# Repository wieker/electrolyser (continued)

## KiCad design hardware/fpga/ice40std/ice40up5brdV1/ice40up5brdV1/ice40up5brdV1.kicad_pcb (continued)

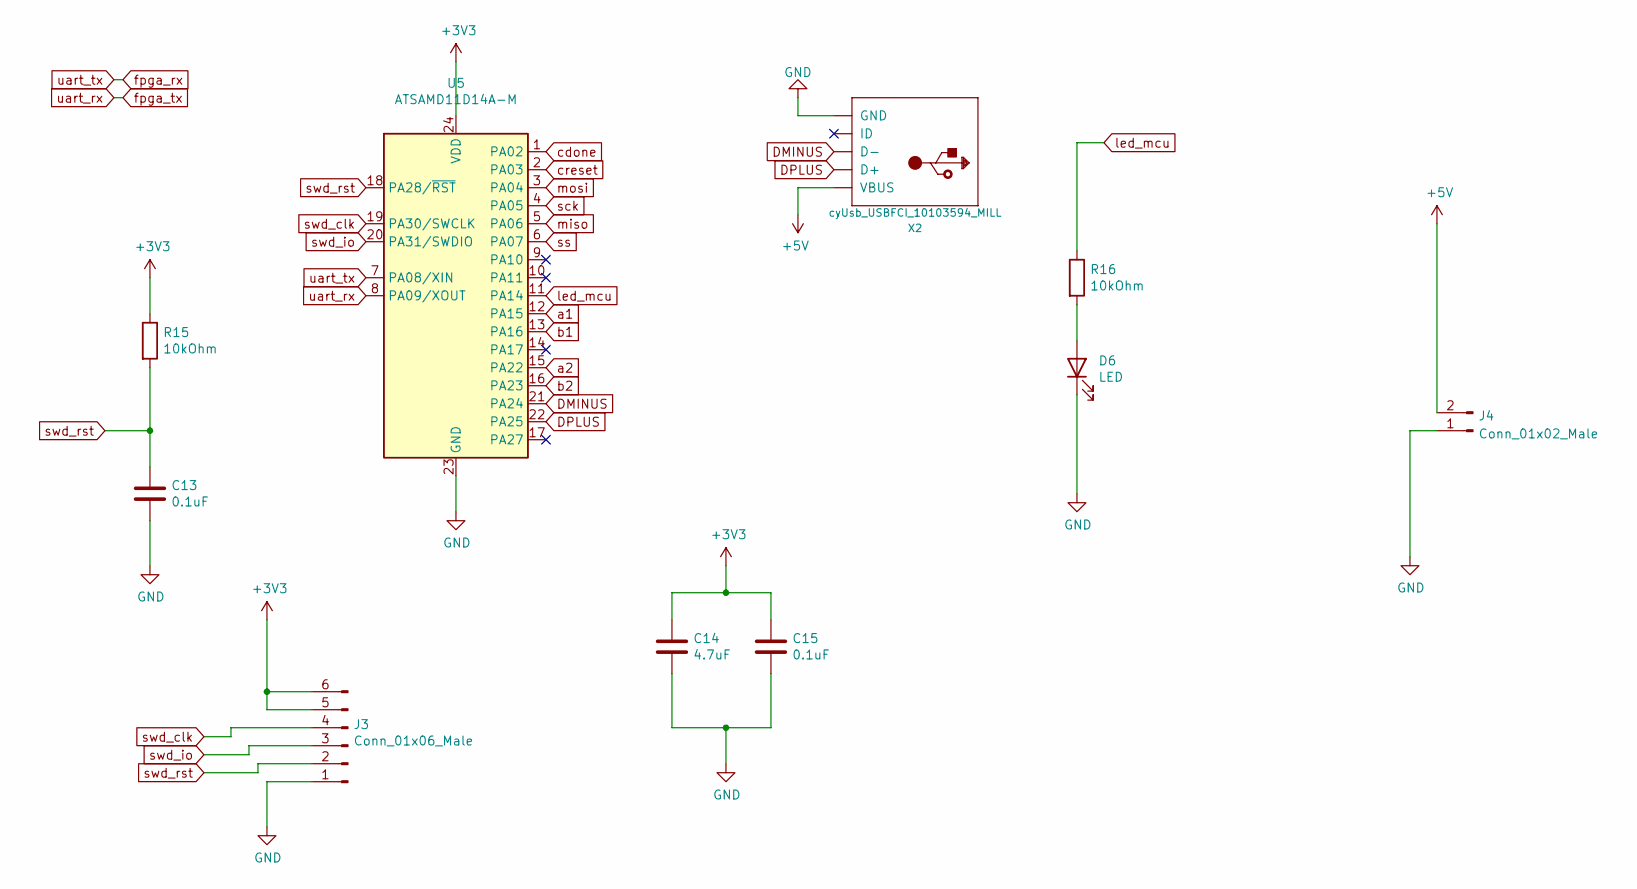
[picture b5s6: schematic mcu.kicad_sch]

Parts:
C13, C15: 0.1uF; C_0402_1005Metric
C14: 4.7uF; C_0402_1005Metric
D6: LED; LED_1206_3216Metric
J3: Conn_01x06_Male; PinHeader_1x06_P2.54mm_Vertical
J4: Conn_01x02_Male; PinHeader_1x02_P2.54mm_Horizontal
R15, R16: 10kOhm; R_0402_1005Metric
U5: ATSAMD11D14A-M; QFN-24-1EP_4x4mm_P0.5mm_EP2.6x2.6mm
X2: cyUsb_USBFCI_10103594_MILL; FCI_10103594_MILL

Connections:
+3V3: C14.1, C15.1, J3.5, J3.6, R15.1, U5.24 (VDD); also elsewhere on the board
+5V: J4.2, X2.VBUS; also elsewhere on the board
DMINUS: U5.21 (PA24), X2.D-
DPLUS: U5.22 (PA25), X2.D+
GND: C13.2, C14.2, C15.2, D6.1 (K), J3.1, J4.1, U5.23 (GND), X2.BASE@1 (GND), X2.BASE@2 (GND), X2.GND, X2.SPRT@1 (GND), X2.SPRT@2 (GND), X2.SPRT@3 (GND), X2.SPRT@4 (GND); also elsewhere on the board
unnamed: D6.2 (A), R16.2
a1: U5.12 (PA15); also elsewhere on the board
a2: U5.15 (PA22); also elsewhere on the board
b1: U5.13 (PA16); also elsewhere on the board
b2: U5.16 (PA23); also elsewhere on the board
cdone: U5.1 (PA02); also elsewhere on the board
creset: U5.2 (PA03); also elsewhere on the board
fpga_rx: U5.7 (PA08/XIN); also elsewhere on the board
fpga_tx: U5.8 (PA09/XOUT); also elsewhere on the board
led_mcu: R16.1, U5.11 (PA14)
miso: U5.5 (PA06); also elsewhere on the board
mosi: U5.3 (PA04); also elsewhere on the board
sck: U5.4 (PA05); also elsewhere on the board
ss: U5.6 (PA07); also elsewhere on the board
swd_clk: J3.4, U5.19 (PA30/SWCLK)
swd_io: J3.3, U5.20 (PA31/SWDIO)
swd_rst: C13.1, J3.2, R15.2, U5.18 (PA28/~RST)

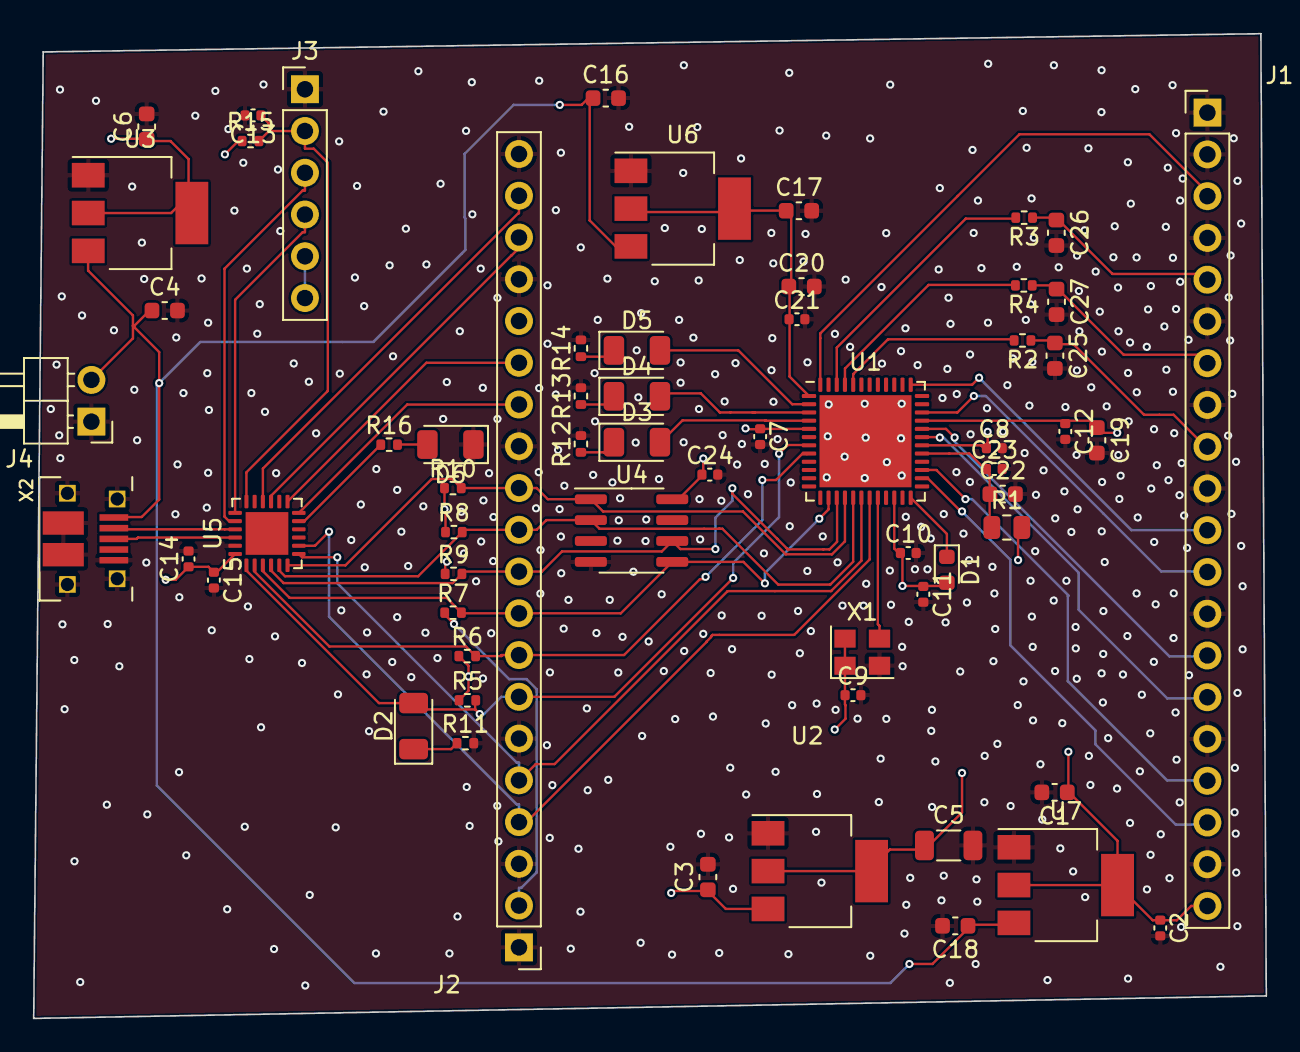
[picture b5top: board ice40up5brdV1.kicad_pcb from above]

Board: 4 copper layers, 75.0 x 59.9 mm, 62 parts (0 on the bottom side), 48 nets.

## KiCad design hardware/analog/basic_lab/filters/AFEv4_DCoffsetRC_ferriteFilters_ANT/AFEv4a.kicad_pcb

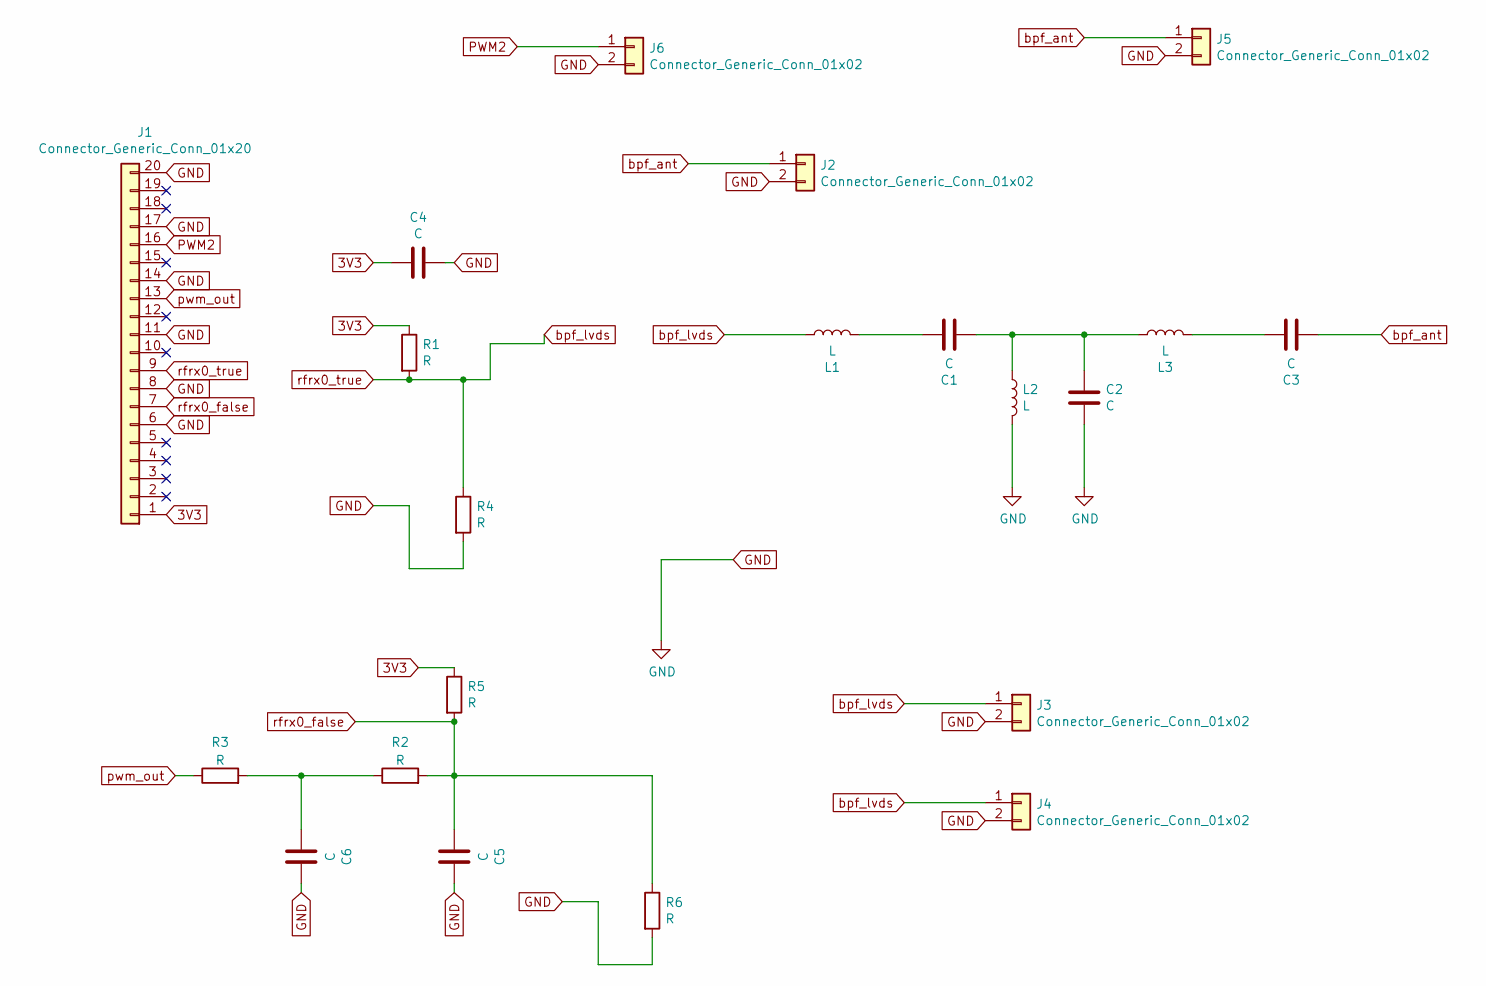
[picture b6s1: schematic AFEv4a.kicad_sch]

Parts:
C1, C2, C3, C4, C5, C6: C; C_Axial_L3.8mm_D2.6mm_P7.50mm_Horizontal
J1: Connector_Generic_Conn_01x20; PinHeader_1x20_P2.54mm_Vertical
J2, J3, J4, J5, J6: Connector_Generic_Conn_01x02; PinHeader_1x02_P2.54mm_Vertical
L1, L2, L3: L; L_Toroid_Horizontal_D12.7mm_P20.00mm_Diameter14-5mm_Amidon-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
R1, R2, R3, R4, R5, R6: R; R_Axial_DIN0207_L6.3mm_D2.5mm_P5.08mm_Vertical

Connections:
3V3: C4.2, J1.1, R1.1, R5.1
GND: C2.2, C4.1, C5.1, C6.1, J1.6, J1.8, J1.11, J1.14, J1.17, J1.20, J2.2, J3.2, J4.2, J5.2, J6.2, L2.2, R4.2, R6.2
unnamed: C1.1, L1.2
unnamed: C1.2, C2.1, L2.1, L3.1
unnamed: C3.1, L3.2
unnamed: C6.2, R2.1, R3.2
PWM2: J1.16, J6.1
bpf_ant: C3.2, J2.1, J5.1
bpf_lvds: J1.9, J3.1, J4.1, L1.1, R1.2, R4.1
pwm_out: J1.13, R3.1
rfrx0_false: C5.2, J1.7, R2.2, R5.2, R6.1

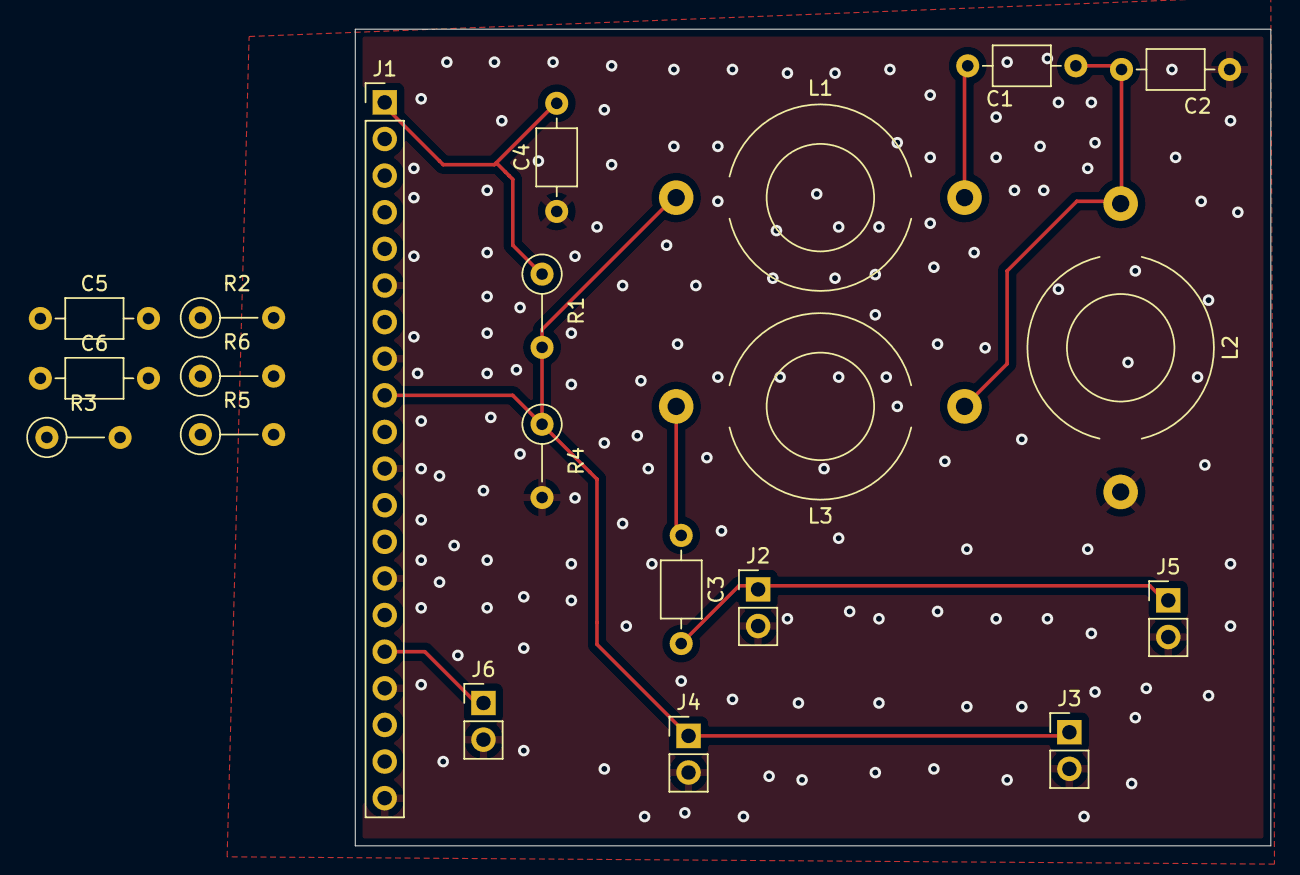
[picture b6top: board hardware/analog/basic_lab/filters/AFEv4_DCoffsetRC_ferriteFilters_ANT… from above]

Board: 2 copper layers, 63.5 x 56.6 mm, 21 parts (0 on the bottom side), 11 nets.

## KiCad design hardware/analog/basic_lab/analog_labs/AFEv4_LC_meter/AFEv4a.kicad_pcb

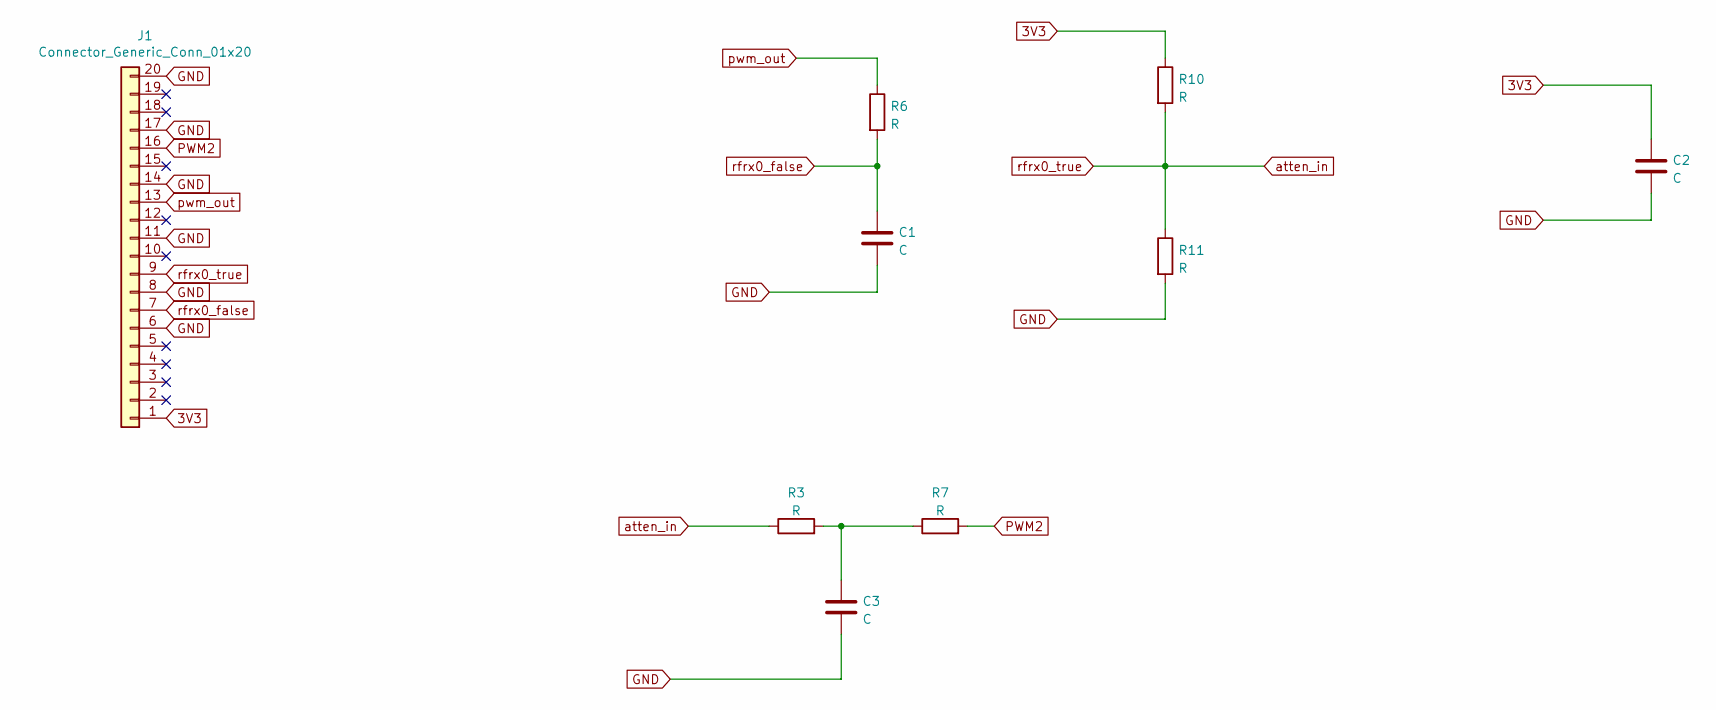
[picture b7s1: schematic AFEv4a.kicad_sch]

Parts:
C1, C2: C; C_Axial_L3.8mm_D2.6mm_P7.50mm_Horizontal
C3: C; PinSocket_1x02_P2.54mm_Vertical
J1: Connector_Generic_Conn_01x20; PinHeader_1x20_P2.54mm_Vertical
R3, R7: R; PinSocket_1x02_P2.54mm_Vertical
R6, R10, R11: R; R_Axial_DIN0309_L9.0mm_D3.2mm_P12.70mm_Horizontal

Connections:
3V3: C2.1, J1.1, R10.1
GND: C1.2, C2.2, C3.2, J1.6, J1.8, J1.11, J1.14, J1.17, J1.20, R11.2
unnamed: C3.1, R3.2, R7.1
PWM2: J1.16, R7.2
atten_in: J1.9, R3.1, R10.2, R11.1
pwm_out: J1.13, R6.1
rfrx0_false: C1.1, J1.7, R6.2

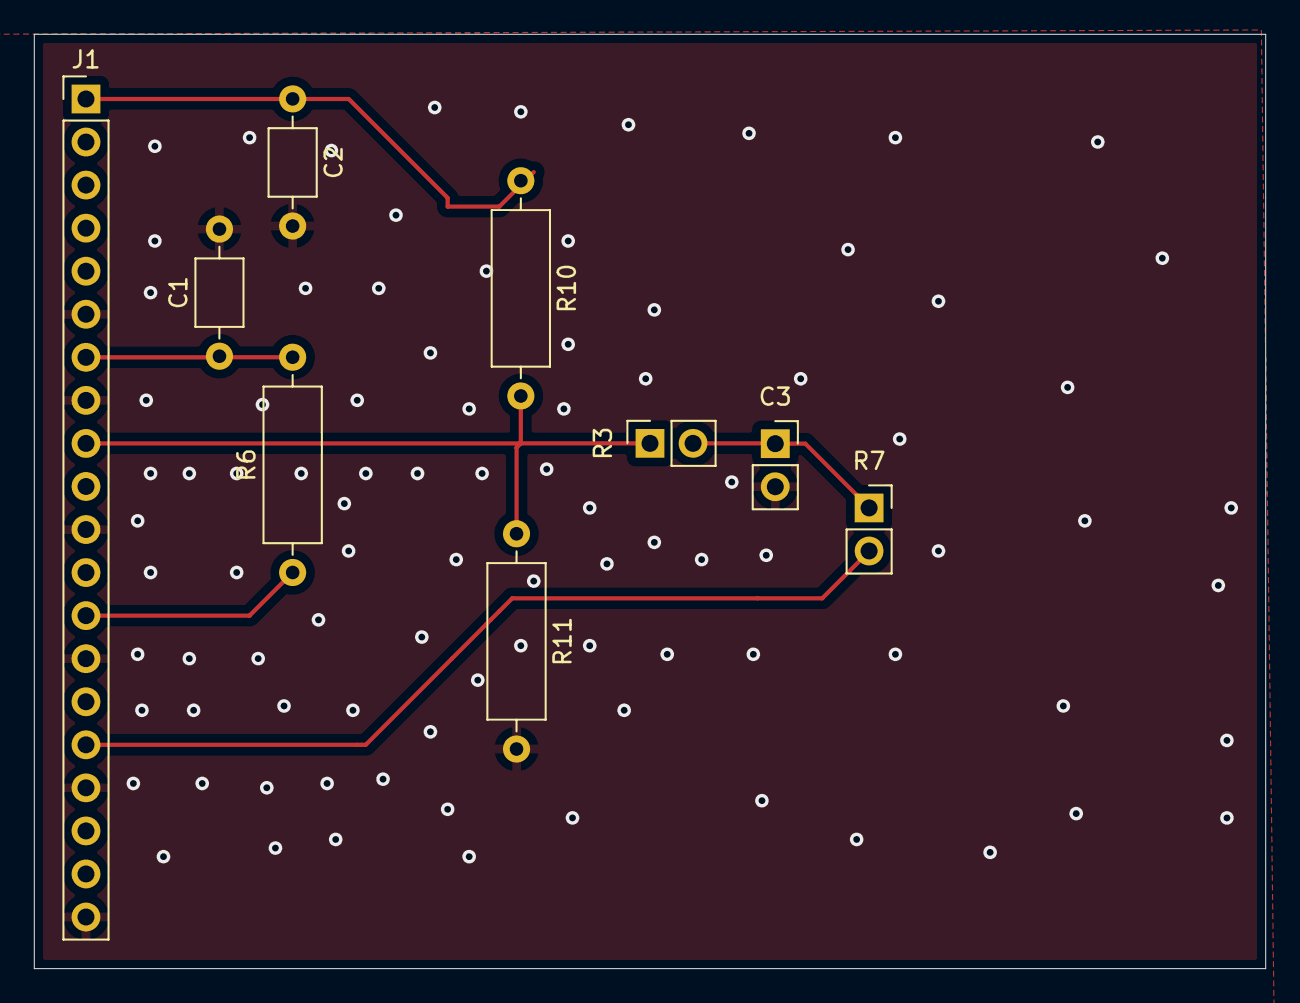
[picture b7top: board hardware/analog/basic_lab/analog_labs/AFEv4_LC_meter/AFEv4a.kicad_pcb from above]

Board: 2 copper layers, 72.6 x 55.1 mm, 9 parts (0 on the bottom side), 7 nets.

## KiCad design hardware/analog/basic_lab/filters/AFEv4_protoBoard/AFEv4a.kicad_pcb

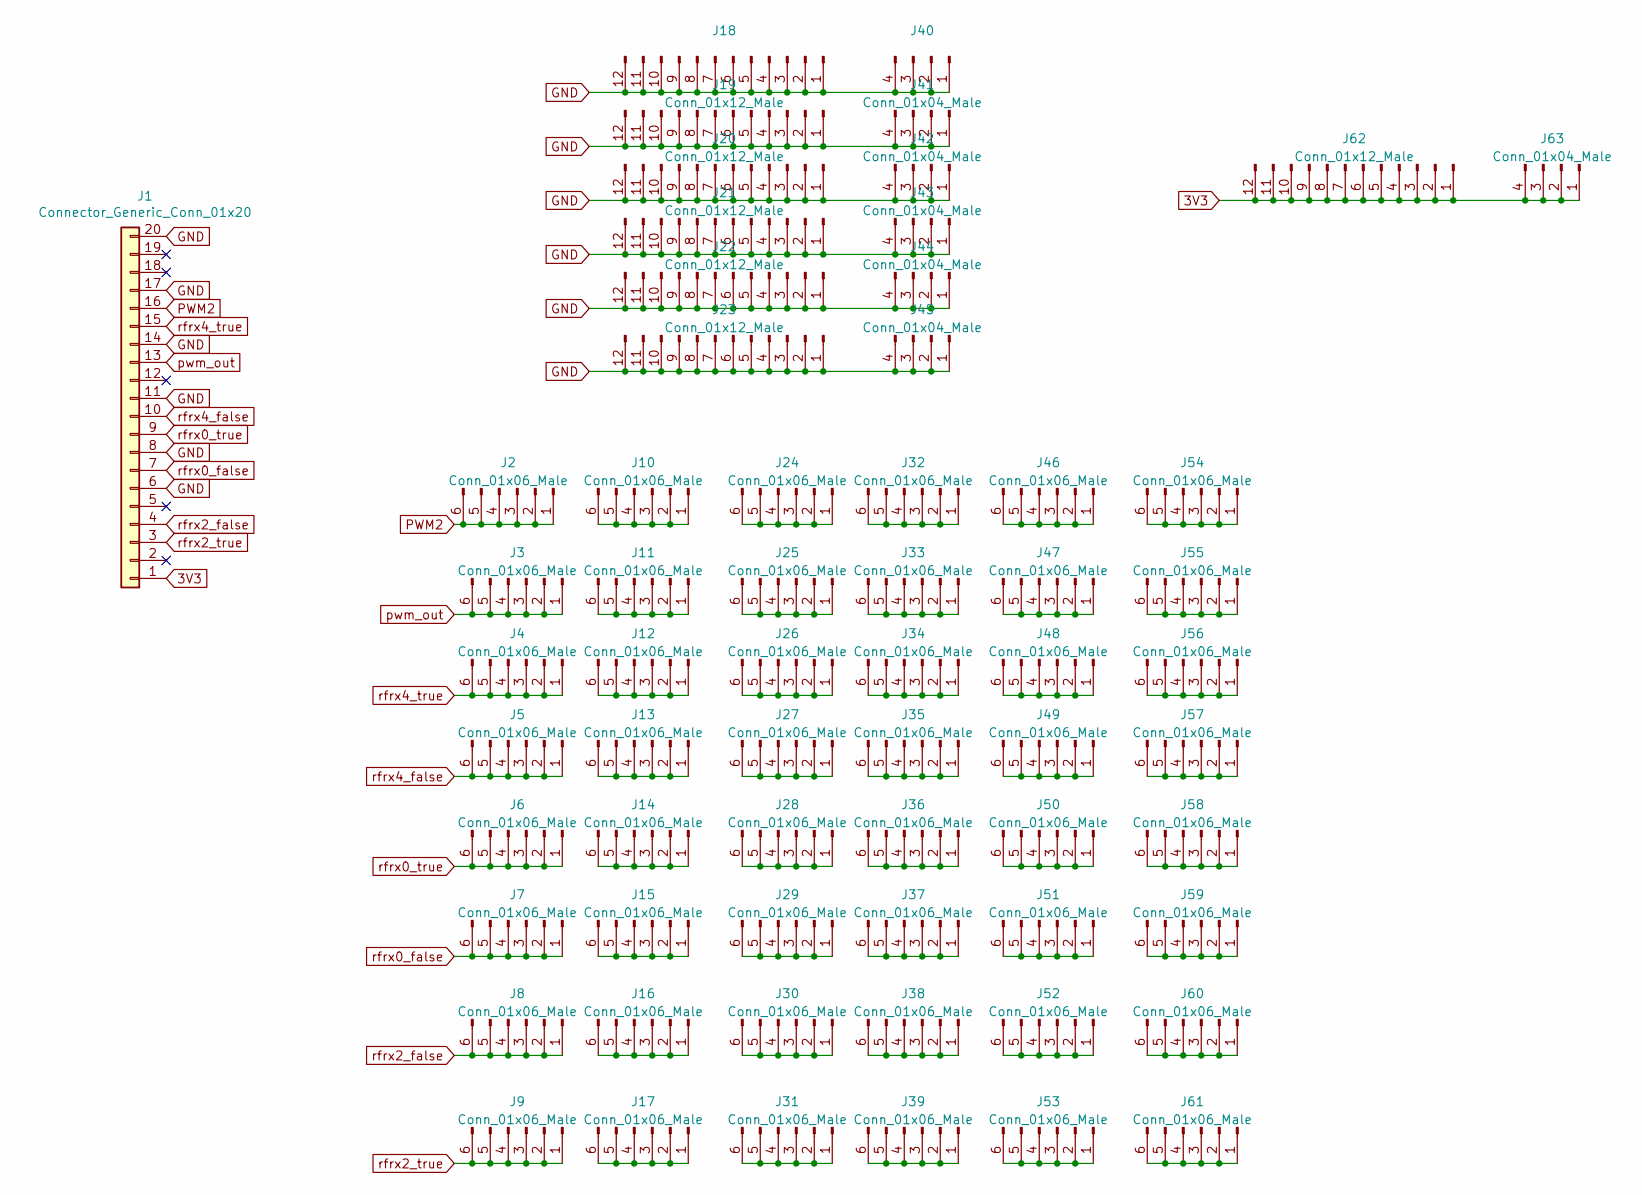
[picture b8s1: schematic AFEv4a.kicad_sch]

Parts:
J1: Connector_Generic_Conn_01x20; PinHeader_1x20_P2.54mm_Vertical
J2: Conn_01x06_Male; PinHeader_1x06_P2.54mm_Vertical
J3, J4, J5, J6, J7, J8, J9, J10, J11, J12, J13, J14, J15, J16, J17, J24, J25, J26, J27, J28, J29, J30, J31, J32, J33, J34, J35, J36, J37, J38, J39, J46, J47, J48, J49, J50, J51, J52, J53, J54, J55, J56, J57, J58, J59, J60, J61: Conn_01x06_Male
J18, J40: (no value)
J19, J20, J21, J22, J23, J62: Conn_01x12_Male
J41, J42, J43, J44, J45, J63: Conn_01x04_Male

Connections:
3V3: J1.1, J62.1, J62.2, J62.3, J62.4, J62.5, J62.6, J62.7, J62.8, J62.9, J62.10, J62.11, J62.12, J63.1, J63.2, J63.3, J63.4
GND: J1.6, J1.8, J1.11, J1.14, J1.17, J1.20, J18.1, J18.2, J18.3, J18.4, J18.5, J18.6, J18.7, J18.8, J18.9, J18.10, J18.11, J18.12, J19.1, J19.2, J19.3, J19.4, J19.5, J19.6, J19.7, J19.8, J19.9, J19.10, J19.11, J19.12, J20.1, J20.2, J20.3, J20.4, J20.5, J20.6, J20.7, J20.8, J20.9, J20.10, J20.11, J20.12, J21.1, J21.2, J21.3, J21.4, J21.5, J21.6, J21.7, J21.8, J21.9, J21.10, J21.11, J21.12, J22.1, J22.2, J22.3, J22.4, J22.5, J22.6, J22.7, J22.8, J22.9, J22.10, J22.11, J22.12, J23.1, J23.2, J23.3, J23.4, J23.5, J23.6, J23.7, J23.8, J23.9, J23.10, J23.11, J23.12, J40.1, J40.2, J40.3, J40.4, J41.1, J41.2, J41.3, J41.4, J42.1, J42.2, J42.3, J42.4, J43.1, J43.2, J43.3, J43.4, J44.1, J44.2, J44.3, J44.4, J45.1, J45.2, J45.3, J45.4
unnamed: J10.1, J10.2, J10.3, J10.4, J10.5, J10.6
unnamed: J11.1, J11.2, J11.3, J11.4, J11.5, J11.6
unnamed: J12.1, J12.2, J12.3, J12.4, J12.5, J12.6
unnamed: J13.1, J13.2, J13.3, J13.4, J13.5, J13.6
unnamed: J14.1, J14.2, J14.3, J14.4, J14.5, J14.6
unnamed: J15.1, J15.2, J15.3, J15.4, J15.5, J15.6
unnamed: J16.1, J16.2, J16.3, J16.4, J16.5, J16.6
unnamed: J17.1, J17.2, J17.3, J17.4, J17.5, J17.6
unnamed: J24.1, J24.2, J24.3, J24.4, J24.5, J24.6
unnamed: J25.1, J25.2, J25.3, J25.4, J25.5, J25.6
unnamed: J26.1, J26.2, J26.3, J26.4, J26.5, J26.6
unnamed: J27.1, J27.2, J27.3, J27.4, J27.5, J27.6
unnamed: J28.1, J28.2, J28.3, J28.4, J28.5, J28.6
unnamed: J29.1, J29.2, J29.3, J29.4, J29.5, J29.6
unnamed: J30.1, J30.2, J30.3, J30.4, J30.5, J30.6
unnamed: J31.1, J31.2, J31.3, J31.4, J31.5, J31.6
unnamed: J32.1, J32.2, J32.3, J32.4, J32.5, J32.6
unnamed: J33.1, J33.2, J33.3, J33.4, J33.5, J33.6
unnamed: J34.1, J34.2, J34.3, J34.4, J34.5, J34.6
unnamed: J35.1, J35.2, J35.3, J35.4, J35.5, J35.6
unnamed: J36.1, J36.2, J36.3, J36.4, J36.5, J36.6
unnamed: J37.1, J37.2, J37.3, J37.4, J37.5, J37.6
unnamed: J38.1, J38.2, J38.3, J38.4, J38.5, J38.6
unnamed: J39.1, J39.2, J39.3, J39.4, J39.5, J39.6
unnamed: J46.1, J46.2, J46.3, J46.4, J46.5, J46.6
unnamed: J47.1, J47.2, J47.3, J47.4, J47.5, J47.6
unnamed: J48.1, J48.2, J48.3, J48.4, J48.5, J48.6
unnamed: J49.1, J49.2, J49.3, J49.4, J49.5, J49.6
unnamed: J50.1, J50.2, J50.3, J50.4, J50.5, J50.6
unnamed: J51.1, J51.2, J51.3, J51.4, J51.5, J51.6
unnamed: J52.1, J52.2, J52.3, J52.4, J52.5, J52.6
unnamed: J53.1, J53.2, J53.3, J53.4, J53.5, J53.6
unnamed: J54.1, J54.2, J54.3, J54.4, J54.5, J54.6
unnamed: J55.1, J55.2, J55.3, J55.4, J55.5, J55.6
unnamed: J56.1, J56.2, J56.3, J56.4, J56.5, J56.6
unnamed: J57.1, J57.2, J57.3, J57.4, J57.5, J57.6
unnamed: J58.1, J58.2, J58.3, J58.4, J58.5, J58.6
unnamed: J59.1, J59.2, J59.3, J59.4, J59.5, J59.6
unnamed: J60.1, J60.2, J60.3, J60.4, J60.5, J60.6
unnamed: J61.1, J61.2, J61.3, J61.4, J61.5, J61.6
PWM2: J1.16, J2.1, J2.2, J2.3, J2.4, J2.5, J2.6
pwm_out: J1.13, J3.1, J3.2, J3.3, J3.4, J3.5, J3.6
rfrx0_false: J1.7, J7.1, J7.2, J7.3, J7.4, J7.5, J7.6
rfrx0_true: J1.9, J6.1, J6.2, J6.3, J6.4, J6.5, J6.6
rfrx2_false: J1.4, J8.1, J8.2, J8.3, J8.4, J8.5, J8.6
rfrx2_true: J1.3, J9.1, J9.2, J9.3, J9.4, J9.5, J9.6
rfrx4_false: J1.10, J5.1, J5.2, J5.3, J5.4, J5.5, J5.6
rfrx4_true: J1.15, J4.1, J4.2, J4.3, J4.4, J4.5, J4.6

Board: 2 copper layers, 63 parts (0 on the bottom side), 50 nets, no tracks yet.

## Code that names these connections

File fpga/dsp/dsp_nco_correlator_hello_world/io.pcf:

set_io LED1 42
set_io LED2 43
set_io btn1 44
set_io btn2 45


set_io lvds_in 32

set_io fpga_tx 19
set_io fpga_rx 18

set_io pwm_out 34

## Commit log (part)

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2023-11-18 timer => adc
2023-11-20 debug mtask
2023-11-25 debug 1d
2023-12-13 debug fuse
2024-02-11 debug monitor
2024-04-13 debug GPIO capture from example
2024-04-15 debug speed timer
2024-04-20 debug PWM capture
2024-04-21 debug PWM capture board2board
2024-04-21 fix broken IO pin on one of the boards
2024-04-21 fix UART logging build
2024-04-22 init board2board
2024-04-23 debug speed measure
2024-04-23 debug board2board
2024-04-30 debug speed measure: GPIO state view
2024-05-05 debug UIt/Rld
2024-05-05 fuse UIt/Rld
2024-05-07 removed unused projects
2024-05-07 moved speed projects
2024-07-13 fuse UIt/Rld used Android/nrf52 HEAD
2024-07-20 ADC current monitor
2024-08-08 Added STM32F1 template
2024-08-26 current monitor back-end
2025-01-01 perspective
2025-03-08 improved frame under Wayland
2025-03-08 flash.sh for the SAMD11 through STLink
2025-03-08 tested SPi flash => fpga
2025-03-11 started I2C master for FPGA => OV7670 camera interface
2025-03-11 started FPGA => OV7670 camera interface
2025-03-13 started FPGA => OV7670 test interface
2025-03-15 started FPGA => OV7670 I2C interface
2025-05-03 lambda experiment
2025-05-18 Compiled clash Verilog code
2025-05-23 POV Ray tracing
2025-09-05 hyperfocl calculations
2025-09-05 triangle calculation from focus
2025-11-08 trying to write correct CMake
2025-11-08 trying to start raw2rgb viewer
2025-11-12 TIFF 2 BMP start
2025-11-12 TIFF => demosaic => BMP
2025-11-15 TIFF => demosaic => XYZ => BMP
2025-11-15 TIFF => demosaic => XYZ => gamma => BMP
2025-12-24 FTDI SPI host
2025-12-24 FTDI SPI verilog
2025-12-24 fpga fast SPI ifc
2025-12-25 Java C interpreter
2025-12-25 Java Bridge: custom SPI code
2025-12-25 Java Bridge: custom SPI code. SPi tx/RX stream works!
2025-12-26 Java Bridge: custom SPI code. SPI stream is more stable
2025-12-28 Java Bridge: SPI => dual port ice40 SRAM => SPI. seems to be stable enough...
2025-12-28 Java Bridge: SPI => dual port ice40 SRAM => SPI. seems to be stable enough... less cycles to process
2025-12-28 Java Bridge: SPI => dual port ice40 SRAM => SPI. seems to be stable enough... 3 MHz ??
2025-12-29 Java Bridge: SPI => dual port ice40 SRAM => SPI. prepare DSP => ice40 SRAM => SPI bridge
2025-12-30 Java Bridge: SPI => dual port ice40 SRAM => SPI. prepare NCO => ice40 SRAM => SPI bridge
2025-12-31 Java Bridge: SPI => dual port ice40 SRAM => SPI. prepare LVDS => ice40 SRAM => SPI bridge. dump works
2025-12-31 Java Bridge: SPI => dual port ice40 SRAM => SPI. prepare LVDS => ice40 SRAM => SPI bridge. TX beacon
2026-03-14 Java RAW processor
2026-03-14 Java tokenizer
2026-03-16 https://web.archive.org/web/20260314114226/https://transitional-writes.dreamwidth.org/ Archive
2026-03-29 Galois solver for quintics in numeric way
2026-04-16 theory of inductive inference
2026-04-16 Social network links
2026-04-16 inductive inference
2026-05-04 inductive inference blog
    https://transitional-writes.dreamwidth.org/
    https://web.archive.org/web/20260429213441/https://transitional-writes.dreamwidth.org/
2026-05-24 inductive inference blog
    https://transitional-writes.dreamwidth.org/
    https://web.archive.org/web/20260524030346/https://transitional-writes.dreamwidth.org/
2026-05-29 Geoecology and inductive inference
2026-05-30 Inductive inference blog
